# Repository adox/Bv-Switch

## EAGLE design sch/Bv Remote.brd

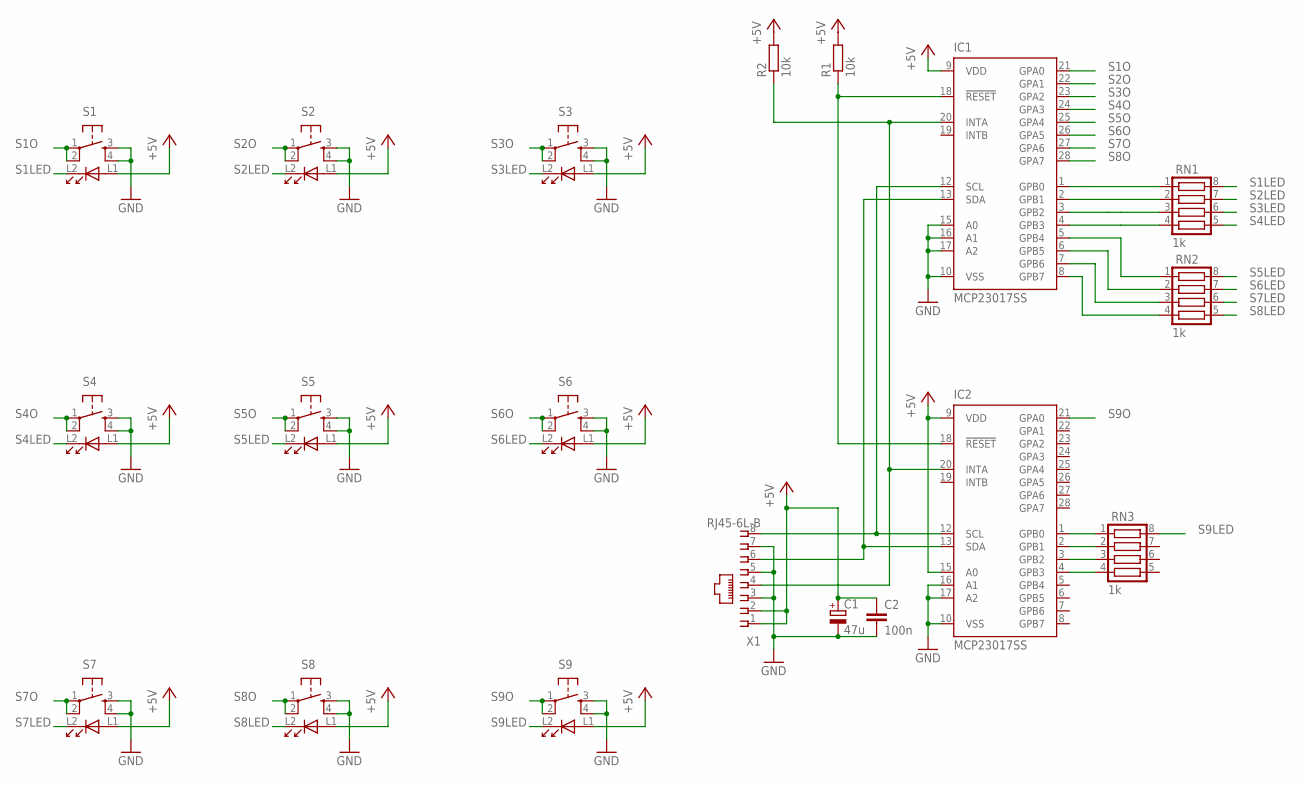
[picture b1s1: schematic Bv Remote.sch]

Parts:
C1: 47u; 153CLV-1010
C2: 100n; C1206
IC1, IC2: MCP23017SS; SSOP28
R1, R2: 10k; R1206
RN1, RN2, RN3: 1k; CTS742C083
S1, S2, S3, S4, S5, S6, S7, S8, S9: TS_HIGHLY_LED; PB614_TACT
X1: RJ45-6L-B; RJ45-NO-SHIELD

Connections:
+5V: C1.+, C2.1, IC1.9 (VDD), IC2.9 (VDD), IC2.15 (A0), R1.2, R2.2, S1.L1 (A), S2.L1 (A), S3.L1 (A), S4.L1 (A), S5.L1 (A), S6.L1 (A), S7.L1 (A), S8.L1 (A), S9.L1 (A), X1.1, X1.2
GND: C1.-, C2.2, IC1.10 (VSS), IC1.15 (A0), IC1.16 (A1), IC1.17 (A2), IC2.10 (VSS), IC2.16 (A1), IC2.17 (A2), S1.3 (S), S1.4 (S1), S2.3 (S), S2.4 (S1), S3.3 (S), S3.4 (S1), S4.3 (S), S4.4 (S1), S5.3 (S), S5.4 (S1), S6.3 (S), S6.4 (S1), S7.3 (S), S7.4 (S1), S8.3 (S), S8.4 (S1), S9.3 (S), S9.4 (S1), X1.3, X1.5, X1.7
unnamed: IC1.1 (GPB0), RN1.1
unnamed: IC1.2 (GPB1), RN1.2
unnamed: IC1.3 (GPB2), RN1.3
unnamed: IC1.4 (GPB3), RN1.4
unnamed: IC1.5 (GPB4), RN2.1
unnamed: IC1.6 (GPB5), RN2.2
unnamed: IC1.7 (GPB6), RN2.3
unnamed: IC1.8 (GPB7), RN2.4
unnamed: IC1.12 (SCL), IC2.12 (SCL), X1.8
unnamed: IC1.13 (SDA), IC2.13 (SDA), X1.6
unnamed: IC1.20 (INTA), IC2.20 (INTA), R2.1, X1.4
unnamed: IC1.18 (!RESET), IC2.18 (!RESET), R1.1
unnamed: IC2.1 (GPB0), RN3.1
unnamed: IC2.2 (GPB1), RN3.2
unnamed: IC2.3 (GPB2), RN3.3
unnamed: IC2.4 (GPB3), RN3.4
S1LED: RN1.8, S1.L2 (C)
S1O: IC1.21 (GPA0), S1.1, S1.2 (P1)
S2LED: RN1.7, S2.L2 (C)
S2O: IC1.22 (GPA1), S2.1, S2.2 (P1)
S3LED: RN1.6, S3.L2 (C)
S3O: IC1.23 (GPA2), S3.1, S3.2 (P1)
S4LED: RN1.5, S4.L2 (C)
S4O: IC1.24 (GPA3), S4.1, S4.2 (P1)
S5LED: RN2.8, S5.L2 (C)
S5O: IC1.25 (GPA4), S5.1, S5.2 (P1)
S6LED: RN2.7, S6.L2 (C)
S6O: IC1.26 (GPA5), S6.1, S6.2 (P1)
S7LED: RN2.6, S7.L2 (C)
S7O: IC1.27 (GPA6), S7.1, S7.2 (P1)
S8LED: RN2.5, S8.L2 (C)
S8O: IC1.28 (GPA7), S8.1, S8.2 (P1)
S9LED: RN3.8, S9.L2 (C)
S9O: IC2.21 (GPA0), S9.1, S9.2 (P1)

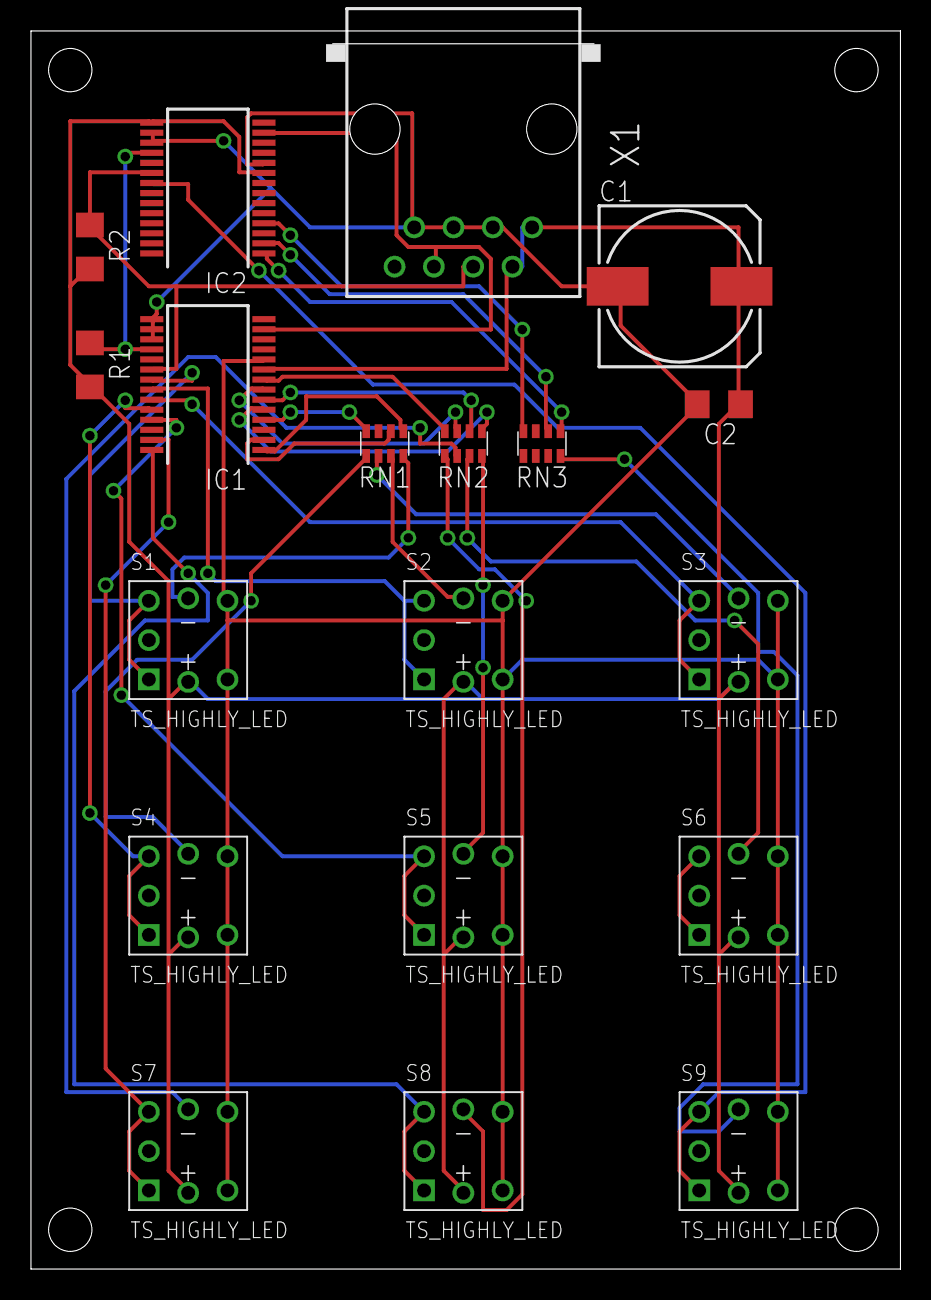
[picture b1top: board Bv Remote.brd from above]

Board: 2 copper layers, 56.2 x 80.0 mm, 19 parts (0 on the bottom side), 36 nets.

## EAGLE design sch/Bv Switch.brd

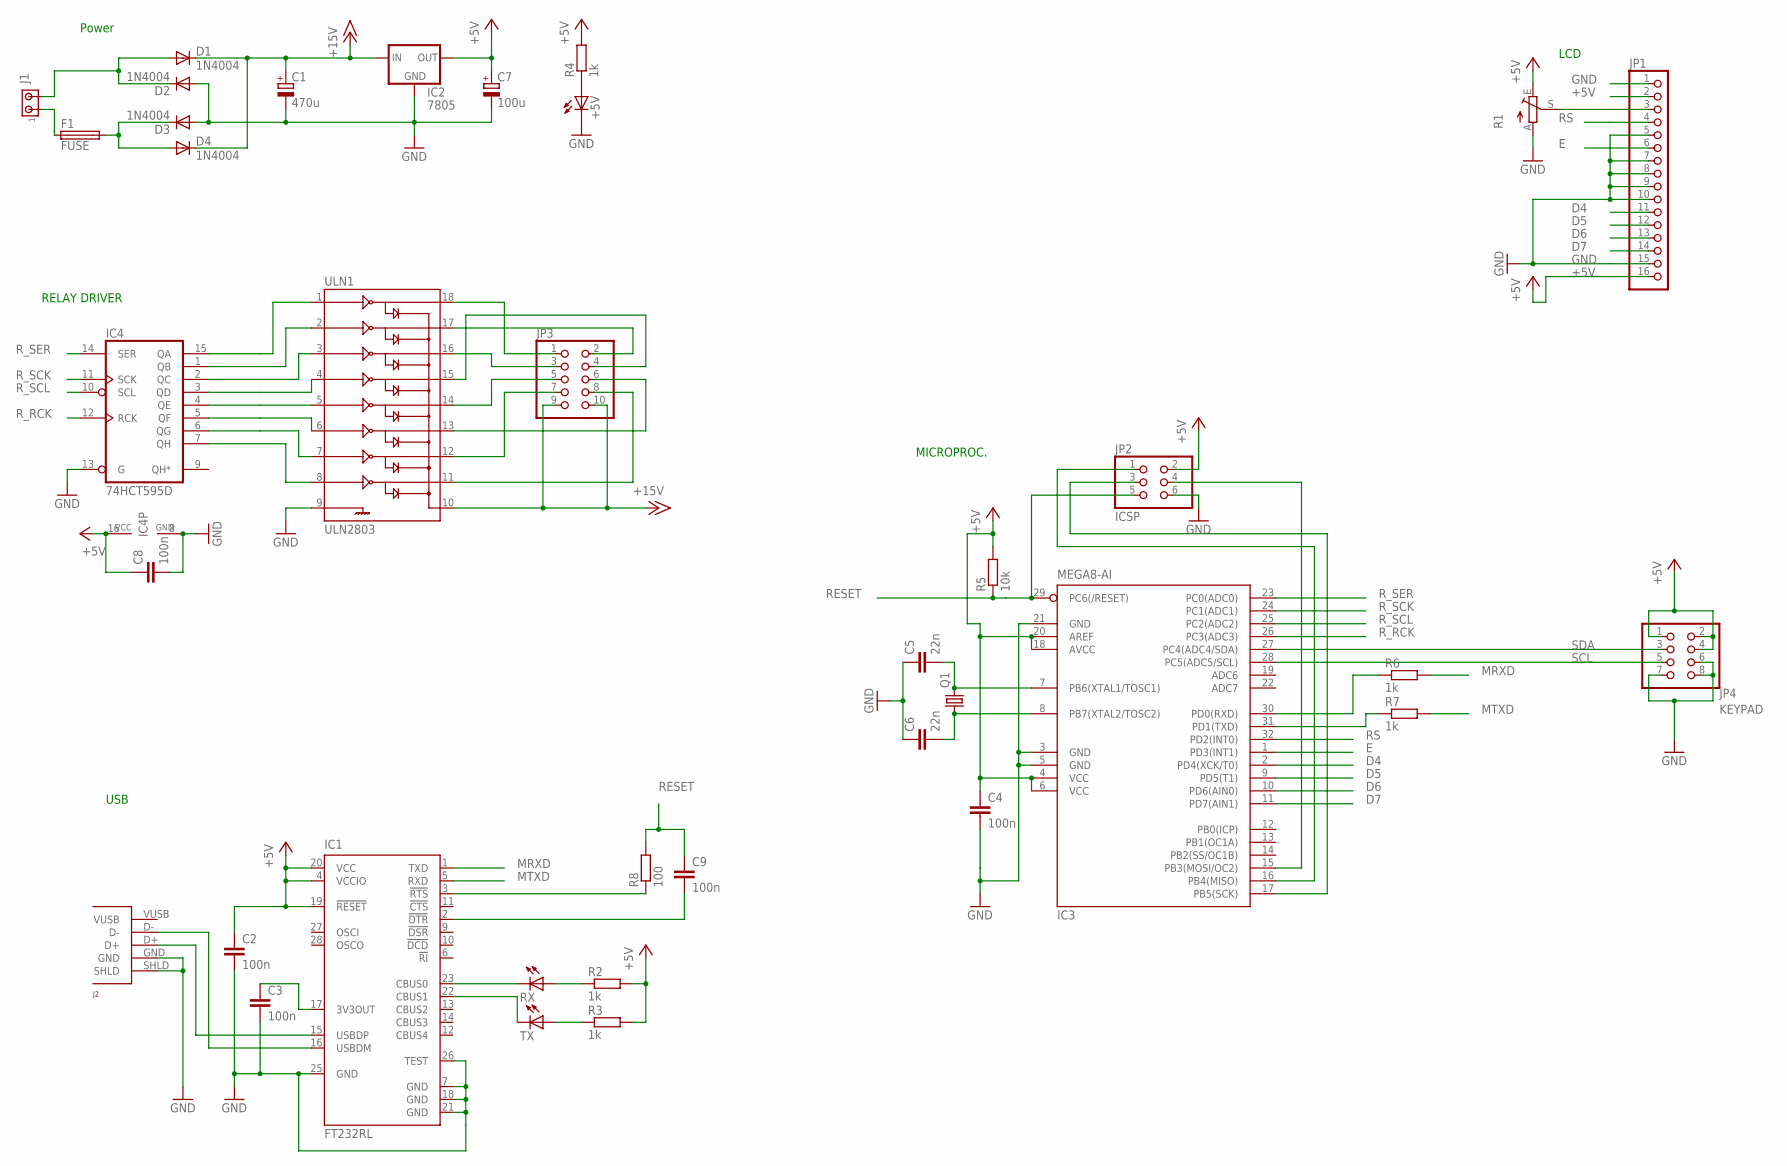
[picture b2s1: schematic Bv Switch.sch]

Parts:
+5V: LEDCHIPLED_1206; CHIPLED_1206
C1: 470u; 153CLV-1010
C2, C3, C4, C8, C9: 100n; C1206
C5, C6: 22n; C1206
C7: 100u; 153CLV-1010
D1, D2, D3, D4: 1N4004; DO41-10
F1: FUSE; FUSE_HOLDER_5X20MM
IC1: FT232RL; SSOP28
IC2: 7805; 78XXL
IC3: MEGA8-AI; TQFP32-08
IC4: 74HCT595D; SO16
J1: MTA02-156; 1X2MTA
J2: USBHD; PINHD4
JP1: PINHD-1X16; 1X16
JP2: ICSP; 2X03
JP3: PINHD-2X5; 2X05
JP4: KEYPAD; 2X04
Q1: CRYSTALSM49; SM49
R1: TRIM_EU-CA6V; CA6V
R2, R3, R4, R6, R7: 1k; R1206
R5: 10k; R1206
R8: 100; R1206
RX: LEDCHIPLED_1206; CHIPLED_1206
TX: LEDCHIPLED_1206; CHIPLED_1206
ULN1: ULN2803; SO018

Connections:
+5V: C2.1, C4.1, C7.+, C8.1, IC1.4 (VCCIO), IC1.19 (!RESET), IC1.20 (VCC), IC2.OUT, IC3.4 (VCC), IC3.6 (VCC), IC3.18 (AVCC), IC3.20 (AREF), IC4.16 (VCC), JP1.2, JP1.16, JP2.2, JP4.1, JP4.2, JP4.4, R1.E, R2.2, R3.2, R4.2, R5.2
+15V: C1.+, D1.C, D4.C, IC2.IN, JP3.9, JP3.10, ULN1.10
D4: IC3.2 (PD4(XCK/T0)), JP1.11
D5: IC3.9 (PD5(T1)), JP1.12
D6: IC3.10 (PD6(AIN0)), JP1.13
D7: IC3.11 (PD7(AIN1)), JP1.14
E: IC3.1 (PD3(INT1)), JP1.6
GND: +5V.C, C1.-, C2.2, C3.2, C4.2, C5.1, C6.1, C7.-, C8.2, D2.A, D3.A, IC1.7 (GND), IC1.18 (GND), IC1.21 (GND), IC1.25 (GND), IC1.26 (TEST), IC2.GND, IC3.3 (GND), IC3.5 (GND), IC3.21 (GND), IC4.8 (GND), IC4.13 (G), J2.GND, J2.SHLD, JP1.1, JP1.5, JP1.7, JP1.8, JP1.9, JP1.10, JP1.15, JP2.6, JP4.6, JP4.7, JP4.8, R1.A, ULN1.9
MRXD: IC1.1 (TXD), R6.2
MTXD: IC1.5 (RXD), R7.2
unnamed: F1.1, J1.1
unnamed: D3.C, D4.A, F1.2
unnamed: D1.A, D2.C, J1.2
unnamed: IC3.17 (PB5(SCK)), JP2.3
unnamed: IC1.15 (USBDP), J2.D+
unnamed: IC1.16 (USBDM), J2.D-
unnamed: +5V.A, R4.1
unnamed: C3.1, IC1.17 (3V3OUT)
unnamed: IC4.15 (QA), ULN1.1
unnamed: IC4.1 (QB), ULN1.2
unnamed: IC1.23 (CBUS0), RX.C
unnamed: IC1.22 (CBUS1), TX.C
unnamed: R2.1, RX.A
unnamed: R3.1, TX.A
unnamed: IC4.2 (QC), ULN1.3
unnamed: C5.2, IC3.7 (PB6(XTAL1/TOSC1)), Q1.2
unnamed: C6.2, IC3.8 (PB7(XTAL2/TOSC2)), Q1.1
unnamed: IC3.16 (PB4(MISO)), JP2.1
unnamed: IC4.3 (QD), ULN1.4
unnamed: IC3.15 (PB3(MOSI/OC2)), JP2.4
unnamed: IC3.30 (PD0(RXD)), R6.1
unnamed: IC3.31 (PD1(TXD)), R7.1
unnamed: IC4.4 (QE), ULN1.5
unnamed: IC4.5 (QF), ULN1.6
unnamed: IC4.6 (QG), ULN1.7
unnamed: IC4.7 (QH), ULN1.8
unnamed: JP3.1, ULN1.18
unnamed: JP3.2, ULN1.17
unnamed: JP3.3, ULN1.16
unnamed: JP3.4, ULN1.15
unnamed: JP3.5, ULN1.14
unnamed: JP3.6, ULN1.13
unnamed: JP3.7, ULN1.12
unnamed: JP3.8, ULN1.11
unnamed: C9.2, IC1.2 (!DTR)
unnamed: IC1.3 (!RTS), R8.1
RESET: C9.1, IC3.29 (PC6(/RESET)), JP2.5, R5.1, R8.2
RS: IC3.32 (PD2(INT0)), JP1.4
R_RCK: IC3.26 (PC3(ADC3)), IC4.12 (RCK)
R_SCK: IC3.24 (PC1(ADC1)), IC4.11 (SCK)
R_SCL: IC3.25 (PC2(ADC2)), IC4.10 (SCL)
R_SER: IC3.23 (PC0(ADC0)), IC4.14 (SER)
SCL: IC3.28 (PC5(ADC5/SCL)), JP4.5
SDA: IC3.27 (PC4(ADC4/SDA)), JP4.3
VO: JP1.3, R1.S

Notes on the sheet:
Power
LCD
USB
MICROPROC.
RELAY DRIVER

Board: 2 copper layers, 37 parts (0 on the bottom side), 55 nets, no tracks yet.

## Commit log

2012-09-20 Reset implementation, initial BRD
2012-09-21 Added Bv-Remote, BRD and 3d generation

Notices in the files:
parts and their libraries:
SparkFun: Licensing: CC v3.0 Share-Alike You are welcome to use this library for commercial purposes.
